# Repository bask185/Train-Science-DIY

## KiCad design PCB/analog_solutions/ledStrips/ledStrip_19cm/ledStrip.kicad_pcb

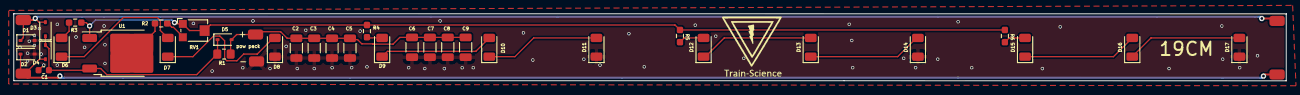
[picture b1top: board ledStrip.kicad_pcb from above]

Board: 2 copper layers, 190.0 x 10.0 mm, 35 parts (0 on the bottom side), 20 nets.

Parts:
AC2: (no value)
C1: 100nF; C_0603_1608Metric
C2, C3, C4, C5, C6, C7, C8, C9: 22uF; C_1206_3216Metric
D1, D2, D3, D4, D5: 1N4148WS; D_SOD-323
D6, D7, D8, D9, D10, D11, D12, D13, D14, D15, D16, D17: LED; LED_1206_3216Metric
R1: 100R; R_0805_handsolder-smalltext
R2: 100R; R_0603_smalltext
R3, R4, R5, R6: 10R; R_0603_smalltext
RV1: 200R; Potentiometer_Bourns_TC33X_Vertical
U1: LM317_TO-252; TO-252-2

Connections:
/Vled: R3.1, R4.1, R5.1, R6.1, RV1.1, RV1.2, U1.1 (ADJ)
AC1: D2.1 (K), D4.2 (A)
AC2: AC2.1, D1.1 (K), D3.2 (A)
GND: C1.2, C2.2, C3.2, C4.2, C5.2, C6.2, C7.2, C8.2, C9.2, D1.2 (A), D2.2 (A), D8.1 (K), D11.1 (K), D14.1 (K), D17.1 (K)
unnamed: C2.1, C3.1, C4.1, C5.1, C6.1, C7.1, C8.1, C9.1, D5.2 (A), R1.1
unnamed: D6.2 (A), R3.2
unnamed: D6.1 (K), D7.2 (A)
unnamed: D7.1 (K), D8.2 (A)
unnamed: D9.2 (A), R4.2
unnamed: D9.1 (K), D10.2 (A)
unnamed: D10.1 (K), D11.2 (A)
unnamed: D12.2 (A), R5.2
unnamed: D12.1 (K), D13.2 (A)
unnamed: D13.1 (K), D14.2 (A)
unnamed: D15.2 (A), R6.2
unnamed: D15.1 (K), D16.2 (A)
unnamed: D16.1 (K), D17.2 (A)
unnamed: R2.2, RV1.3
unnamed: R2.1, U1.2 (VO)
VCC: C1.1, D3.1 (K), D4.1 (K), D5.1 (K), R1.2, U1.3 (VI)

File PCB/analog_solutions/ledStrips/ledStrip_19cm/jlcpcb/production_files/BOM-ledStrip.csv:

Comment,Designator,Footprint,LCSC
22uF,"C2,C3,C4,C5,C6,C7,C8,C9",C_1206_3216Metric,C12891
100nF,C1,C_0603_1608Metric,C14663
100R,R1,R_0805_handsolder-smalltext,C17408
1N4148WS,"D1,D2,D3,D4,D5",D_SOD-323,C2128
LED,"D10,D11,D12,D13,D14,D15,D16,D17,D6,D7,D8,D9",LED_1206_3216Metric,C219232
100R,R2,R_0603_smalltext,C22775
10R,"R3,R4,R5,R6",R_0603_smalltext,C22859
200R,RV1,Potentiometer_Bourns_TC33X_Vertical,C720646
LM317_TO-252,U1,TO-252-2,C75510

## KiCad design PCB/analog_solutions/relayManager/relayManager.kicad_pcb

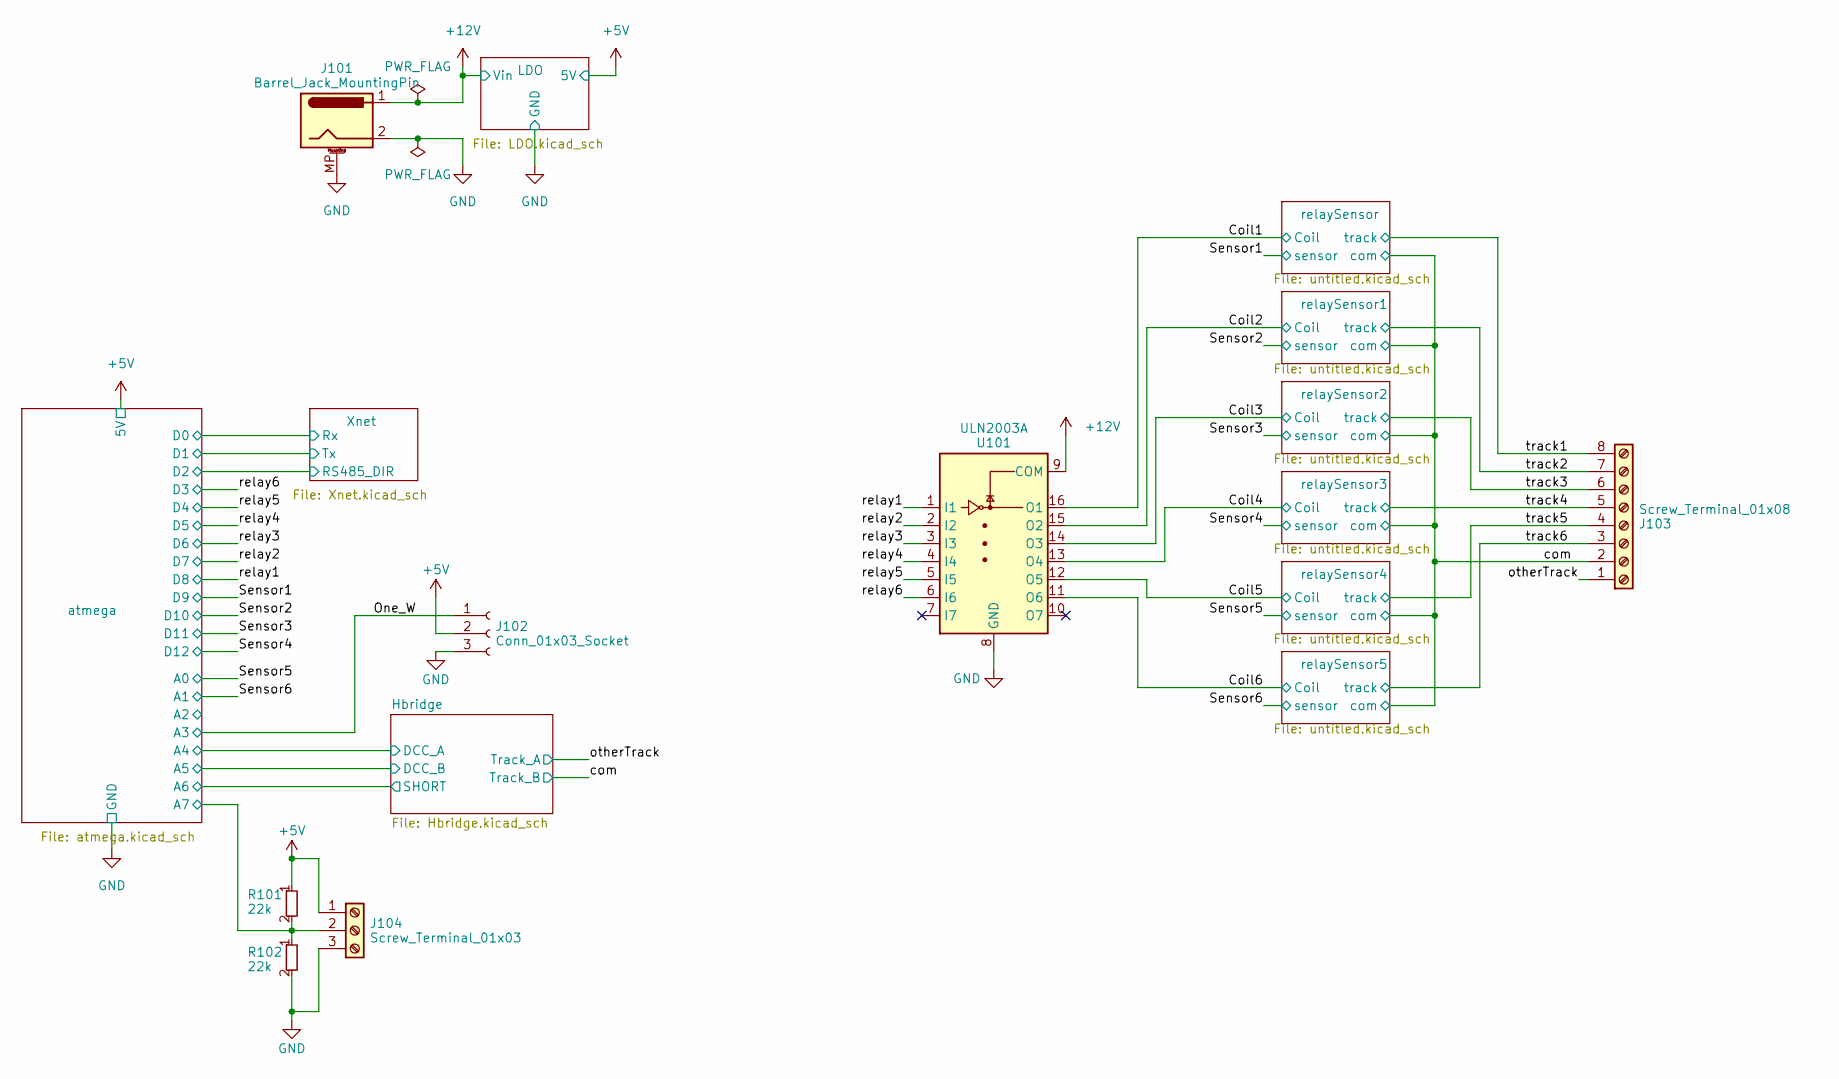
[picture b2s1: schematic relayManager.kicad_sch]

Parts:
J101: Barrel_Jack_MountingPin; barreljack
J102: Conn_01x03_Socket; PinHeader_1x03_P2.54mm_Vertical
J103: Screw_Terminal_01x08; TerminalBlock_Phoenix_MKDS-1,5-8-5.08_1x08_P5.08mm_Horizont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
J104: Screw_Terminal_01x03; TerminalBlock_Phoenix_MKDS-1,5-3-5.08_1x03_P5.08mm_Horizont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
R101, R102: 22k; R_0603_smalltext; JLCPCB Part# C31850
U101: ULN2003A; SOIC-16W_5.3x10.2mm_P1.27mm; JLCPCB Part# C7512

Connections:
+5V: J102.2, J104.1, R101.1; also elsewhere on the board
+12V: J101.1, U101.9 (COM); also elsewhere on the board
/Coil1: U101.16 (O1); also elsewhere on the board
/Coil2: U101.15 (O2); also elsewhere on the board
/Coil3: U101.14 (O3); also elsewhere on the board
/Coil4: U101.13 (O4); also elsewhere on the board
/Coil5: U101.12 (O5); also elsewhere on the board
/Coil6: U101.11 (O6); also elsewhere on the board
/One_W: J102.1; also elsewhere on the board
/atmega/A7: J104.2, R101.2, R102.1; also elsewhere on the board
/com: J103.2; also elsewhere on the board
/otherTrack: J103.1; also elsewhere on the board
/relay1: U101.1 (I1); also elsewhere on the board
/relay2: U101.2 (I2); also elsewhere on the board
/relay3: U101.3 (I3); also elsewhere on the board
/relay4: U101.4 (I4); also elsewhere on the board
/relay5: U101.5 (I5); also elsewhere on the board
/relay6: U101.6 (I6); also elsewhere on the board
/track1: J103.8; also elsewhere on the board
/track2: J103.7; also elsewhere on the board
/track3: J103.6; also elsewhere on the board
/track4: J103.5; also elsewhere on the board
/track5: J103.4; also elsewhere on the board
/track6: J103.3; also elsewhere on the board
GND: J101.2, J101.MP (MountPin), J102.3, J104.3, R102.2, U101.8 (GND); also elsewhere on the board

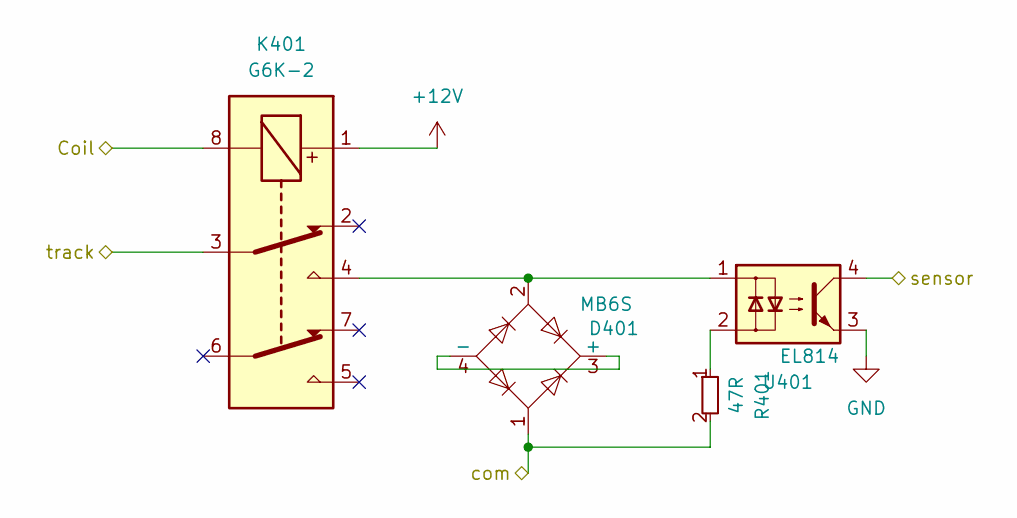
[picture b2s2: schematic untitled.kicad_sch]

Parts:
D401: MB6S; TO-269AA; JLCPCB Part# C2488
K401: G6K-2; Relay_DPDT_Omron_G6K-2F-Y; JLCPCB Part# C397192
R401: 47R; R_0603_smalltext; JLCPCB Part# C23182
U401: EL814; SMDIP-4_W9.53mm; JLCPCB Part# C500388

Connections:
+12V: K401.1; also elsewhere on the board
/Coil1: K401.8; also elsewhere on the board
/Sensor1: U401.4; also elsewhere on the board
/com: D401.1, R401.2; also elsewhere on the board
/track1: K401.3; also elsewhere on the board
GND: U401.3; also elsewhere on the board
unnamed: D401.3 (+), D401.4 (-)
unnamed: D401.2, K401.4, U401.1
unnamed: R401.1, U401.2

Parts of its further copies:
D501, D601, D701, D801, D901: MB6S; TO-269AA; JLCPCB Part# C2488
K501, K601, K701, K801, K901: G6K-2; Relay_DPDT_Omron_G6K-2F-Y; JLCPCB Part# C397192
R501, R601, R701, R801, R901: 47R; R_0603_smalltext; JLCPCB Part# C23182
U501, U601, U701, U801, U901: EL814; SMDIP-4_W9.53mm; JLCPCB Part# C500388

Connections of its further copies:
+12V: K501.1, K601.1, K701.1, K801.1, K901.1; also elsewhere on the board
/Coil2: K501.8; also elsewhere on the board
/Coil3: K601.8; also elsewhere on the board
/Coil4: K701.8; also elsewhere on the board
/Coil5: K801.8; also elsewhere on the board
/Coil6: K901.8; also elsewhere on the board
/Sensor2: U501.4; also elsewhere on the board
/Sensor3: U601.4; also elsewhere on the board
/Sensor4: U701.4; also elsewhere on the board
/Sensor5: U801.4; also elsewhere on the board
/Sensor6: U901.4; also elsewhere on the board
/com: D501.1, D601.1, D701.1, D801.1, D901.1, R501.2, R601.2, R701.2, R801.2, R901.2; also elsewhere on the board
/track2: K501.3; also elsewhere on the board
/track3: K601.3; also elsewhere on the board
/track4: K701.3; also elsewhere on the board
/track5: K801.3; also elsewhere on the board
/track6: K901.3; also elsewhere on the board
GND: U501.3, U601.3, U701.3, U801.3, U901.3; also elsewhere on the board
unnamed: D501.3 (+), D501.4 (-)
unnamed: D501.2, K501.4, U501.1
unnamed: D601.3 (+), D601.4 (-)
unnamed: D601.2, K601.4, U601.1
unnamed: D701.3 (+), D701.4 (-)
unnamed: D701.2, K701.4, U701.1
unnamed: D801.3 (+), D801.4 (-)
unnamed: D801.2, K801.4, U801.1
unnamed: D901.3 (+), D901.4 (-)
unnamed: D901.2, K901.4, U901.1
unnamed: R501.1, U501.2
unnamed: R601.1, U601.2
unnamed: R701.1, U701.2
unnamed: R801.1, U801.2
unnamed: R901.1, U901.2

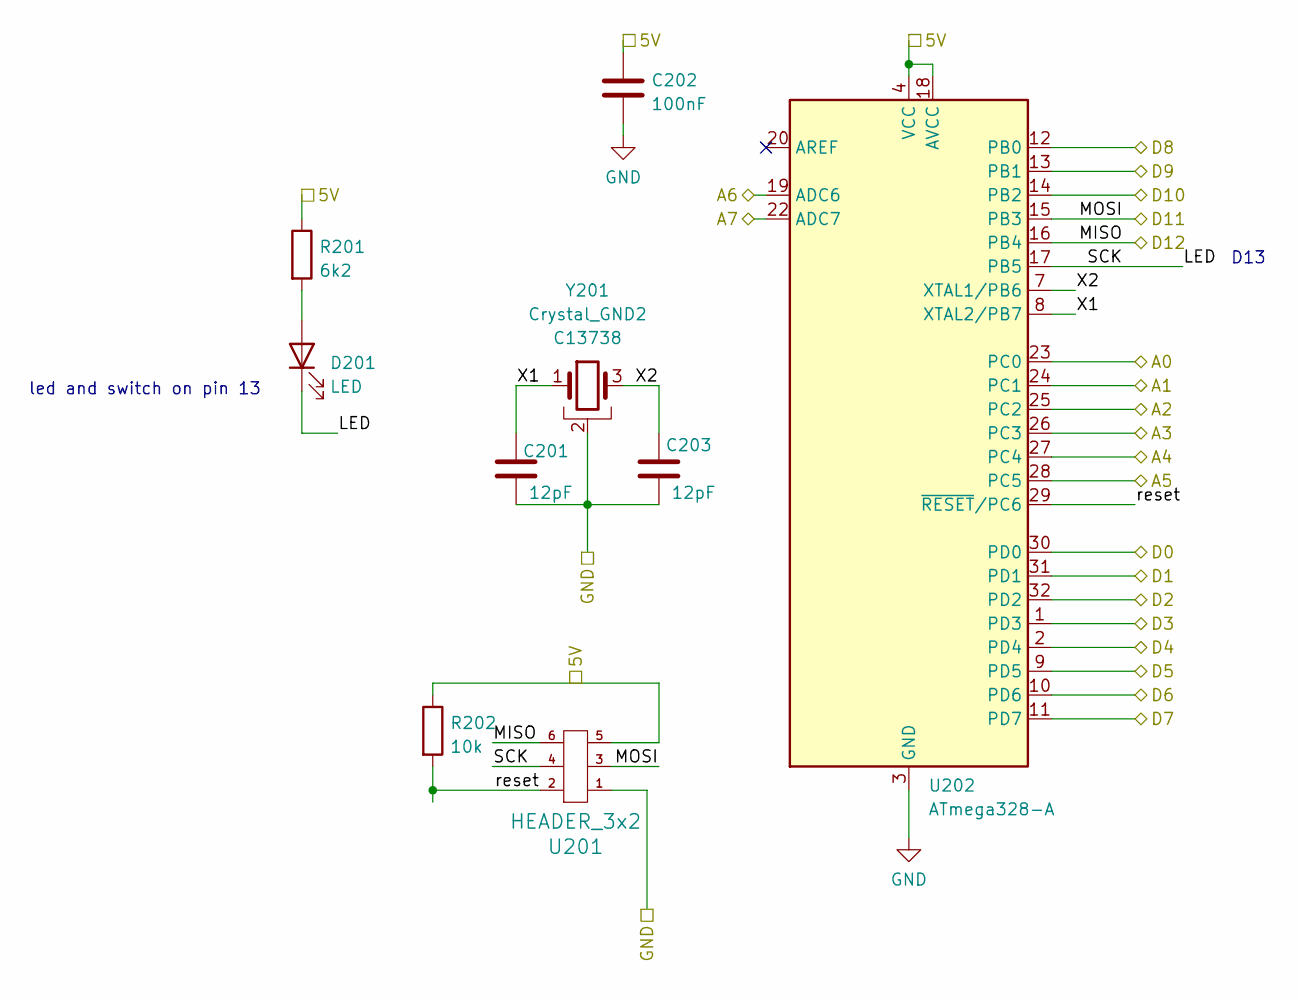
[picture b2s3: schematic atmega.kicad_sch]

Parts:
C201: 12pF; C_0805_2012Metric_Pad1.18x1.45mm_HandSolder
C202: 100nF; C_0603_1608Metric_Pad1.08x0.95mm_HandSolder; JLCPCB Part# C14663
C203: 12pF; C_0805_2012Metric_Pad1.18x1.45mm_HandSolder; JLCPCB Part# C1792
D201: LED; LED_0805_2012Metric_Pad1.15x1.40mm_HandSolder; JLCPCB Part# C84256
R201: 6k2; R_0603_1608Metric_Pad0.98x0.95mm_HandSolder; JLCPCB Part# C4260
R202: 10k; R_0402_1005Metric_Pad0.72x0.64mm_HandSolder; JLCPCB Part# C25744
U201: HEADER_3x2; PinSocket_2x03_P1.27mm_Vertical
U202: ATmega328-A; TQFP-32_7x7mm_P0.8mm; JLCPCB Part# C14877
Y201: Crystal_GND2; crystal_arduino; JLCPCB Part# C13738

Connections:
+5V: C202.2, R201.1, R202.1, U201.5, U202.4 (VCC), U202.6 (VCC), U202.18 (AVCC); also elsewhere on the board
/Hbridge/DCC_A: U202.27 (PC4); also elsewhere on the board
/Hbridge/DCC_B: U202.28 (PC5); also elsewhere on the board
/Hbridge/SHORT: U202.19 (ADC6); also elsewhere on the board
/One_W: U202.26 (PC3); also elsewhere on the board
/Sensor1: U202.13 (PB1); also elsewhere on the board
/Sensor2: U202.14 (PB2); also elsewhere on the board
/Sensor3: U201.3, U202.15 (PB3); also elsewhere on the board
/Sensor4: U201.6, U202.16 (PB4); also elsewhere on the board
/Sensor5: U202.23 (PC0); also elsewhere on the board
/Sensor6: U202.24 (PC1); also elsewhere on the board
/Xnet/RS485_DIR: U202.32 (PD2); also elsewhere on the board
/Xnet/Rx: U202.30 (PD0); also elsewhere on the board
/Xnet/Tx: U202.31 (PD1); also elsewhere on the board
/atmega/A2: U202.25 (PC2)
/atmega/A7: U202.22 (ADC7); also elsewhere on the board
/atmega/LED: D201.1 (K), U201.4, U202.17 (PB5)
/atmega/X1: C201.2, U202.8 (XTAL2/PB7), Y201.1
/atmega/X2: C203.2, U202.7 (XTAL1/PB6), Y201.3
/atmega/reset: R202.2, U201.2, U202.29 (~RESET/PC6)
/relay1: U202.12 (PB0); also elsewhere on the board
/relay2: U202.11 (PD7); also elsewhere on the board
/relay3: U202.10 (PD6); also elsewhere on the board
/relay4: U202.9 (PD5); also elsewhere on the board
/relay5: U202.2 (PD4); also elsewhere on the board
/relay6: U202.1 (PD3); also elsewhere on the board
GND: C201.1, C202.1, C203.1, U201.1, U202.3 (GND), U202.5 (GND), U202.21 (GND), Y201.2 (GND), Y201.4 (GND); also elsewhere on the board
unnamed: D201.2 (A), R201.2

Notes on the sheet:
led and switch on pin 13
D13

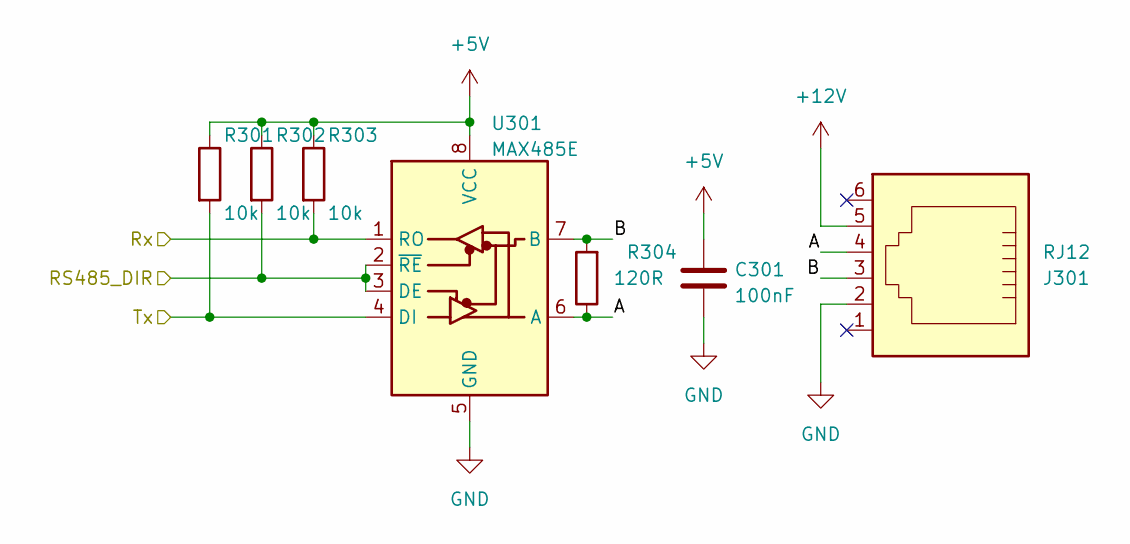
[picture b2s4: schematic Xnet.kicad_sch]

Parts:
C301: 100nF; C_0603_1608Metric; JLCPCB Part# C14663
J301: RJ12
R301, R302, R303: 10k; R_0402_1005Metric; JLCPCB Part# C25744
R304: 120R; R_0805_2012Metric
U301: MAX485E; SOIC-8_3.9x4.9mm_P1.27mm; JLCPCB Part# C668206

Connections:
+5V: C301.1, R301.1, R302.1, R303.1, U301.8 (VCC); also elsewhere on the board
+12V: J301.5; also elsewhere on the board
/Xnet/A: J301.4, R304.1, U301.6 (A)
/Xnet/B: J301.3, R304.2, U301.7 (B)
/Xnet/RS485_DIR: R302.2, U301.2 (~RE), U301.3 (DE); also elsewhere on the board
/Xnet/Rx: R303.2, U301.1 (RO); also elsewhere on the board
/Xnet/Tx: R301.2, U301.4 (DI); also elsewhere on the board
GND: C301.2, J301.2, U301.5 (GND); also elsewhere on the board

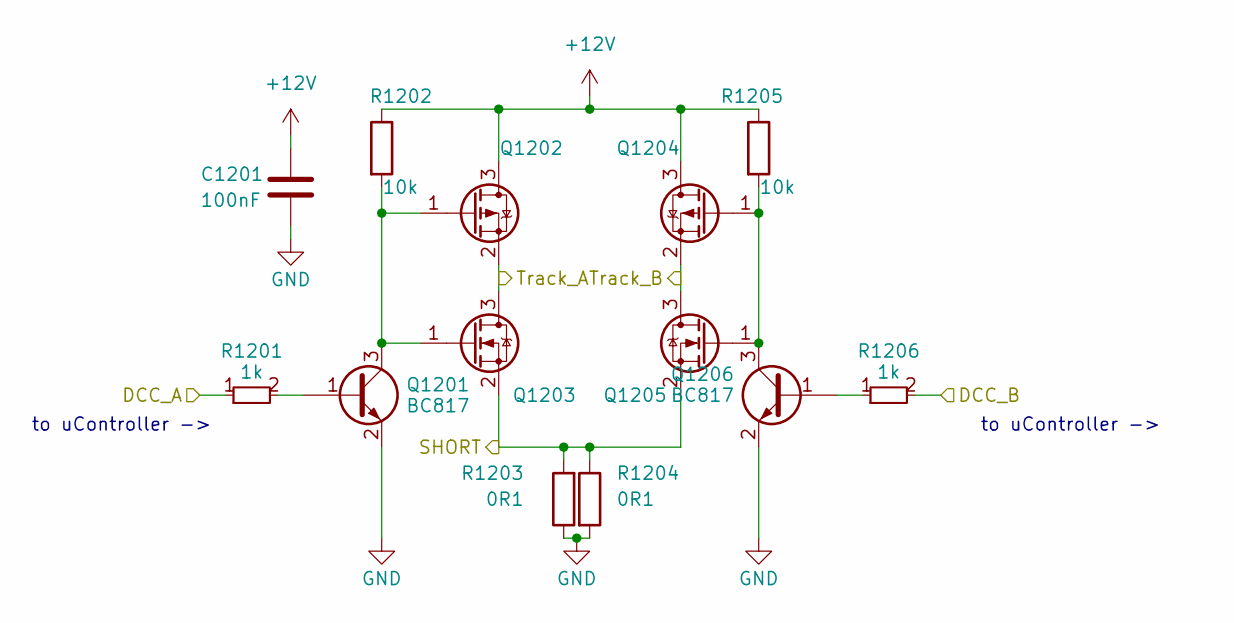
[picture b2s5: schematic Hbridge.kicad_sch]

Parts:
C1201: 100nF; C_0603_1608Metric_Pad1.08x0.95mm_HandSolder; JLCPCB Part# C14663
Q1201, Q1206: BC817; SOT-23; JLCPCB Part# C181140
Q1202, Q1204: P-channel; SOT-23
Q1203: N-Channel; SOT-23
Q1205: N-channel; SOT-23
R1201, R1206: 1k; R_0603_smalltext; JLCPCB Part# C21190
R1202, R1205: 10k; R_0603_1608Metric
R1203, R1204: 0R1; R_0805_2012Metric_Pad1.20x1.40mm_HandSolder; JLCPCB Part# C25334

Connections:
+12V: C1201.2, Q1202.3 (D), Q1204.3 (D), R1202.1, R1205.1; also elsewhere on the board
/Hbridge/DCC_A: R1201.1; also elsewhere on the board
/Hbridge/DCC_B: R1206.2; also elsewhere on the board
/Hbridge/SHORT: Q1203.2 (S), Q1205.2 (S), R1203.2, R1204.1; also elsewhere on the board
/com: Q1204.2 (S), Q1205.3 (D); also elsewhere on the board
/otherTrack: Q1202.2 (S), Q1203.3 (D); also elsewhere on the board
GND: C1201.1, Q1201.2 (E), Q1206.2 (E), R1203.1, R1204.2; also elsewhere on the board
unnamed: Q1201.1 (B), R1201.2
unnamed: Q1201.3 (C), Q1202.1 (G), Q1203.1 (G), R1202.2
unnamed: Q1204.1 (G), Q1205.1 (G), Q1206.3 (C), R1205.2
unnamed: Q1206.1 (B), R1206.1

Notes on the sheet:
to uController ->

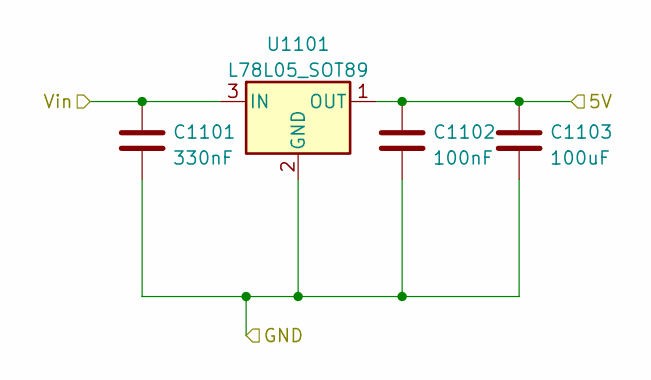
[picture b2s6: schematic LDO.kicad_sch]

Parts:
C1101: 330nF; C_0603_1608Metric_Pad1.08x0.95mm_HandSolder; JLCPCB Part# C1615
C1102: 100nF; C_0603_1608Metric_Pad1.08x0.95mm_HandSolder; JLCPCB Part# C14663
C1103: 100uF; C_1206_3216Metric_Pad1.33x1.80mm_HandSolder; JLCPCB Part# C15008
U1101: L78L05_SOT89; SOT-89-3; JLCPCB Part# C71136

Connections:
+5V: C1102.1, C1103.1, U1101.1 (OUT); also elsewhere on the board
+12V: C1101.1, U1101.3 (IN); also elsewhere on the board
GND: C1101.2, C1102.2, C1103.2, U1101.2 (GND); also elsewhere on the board

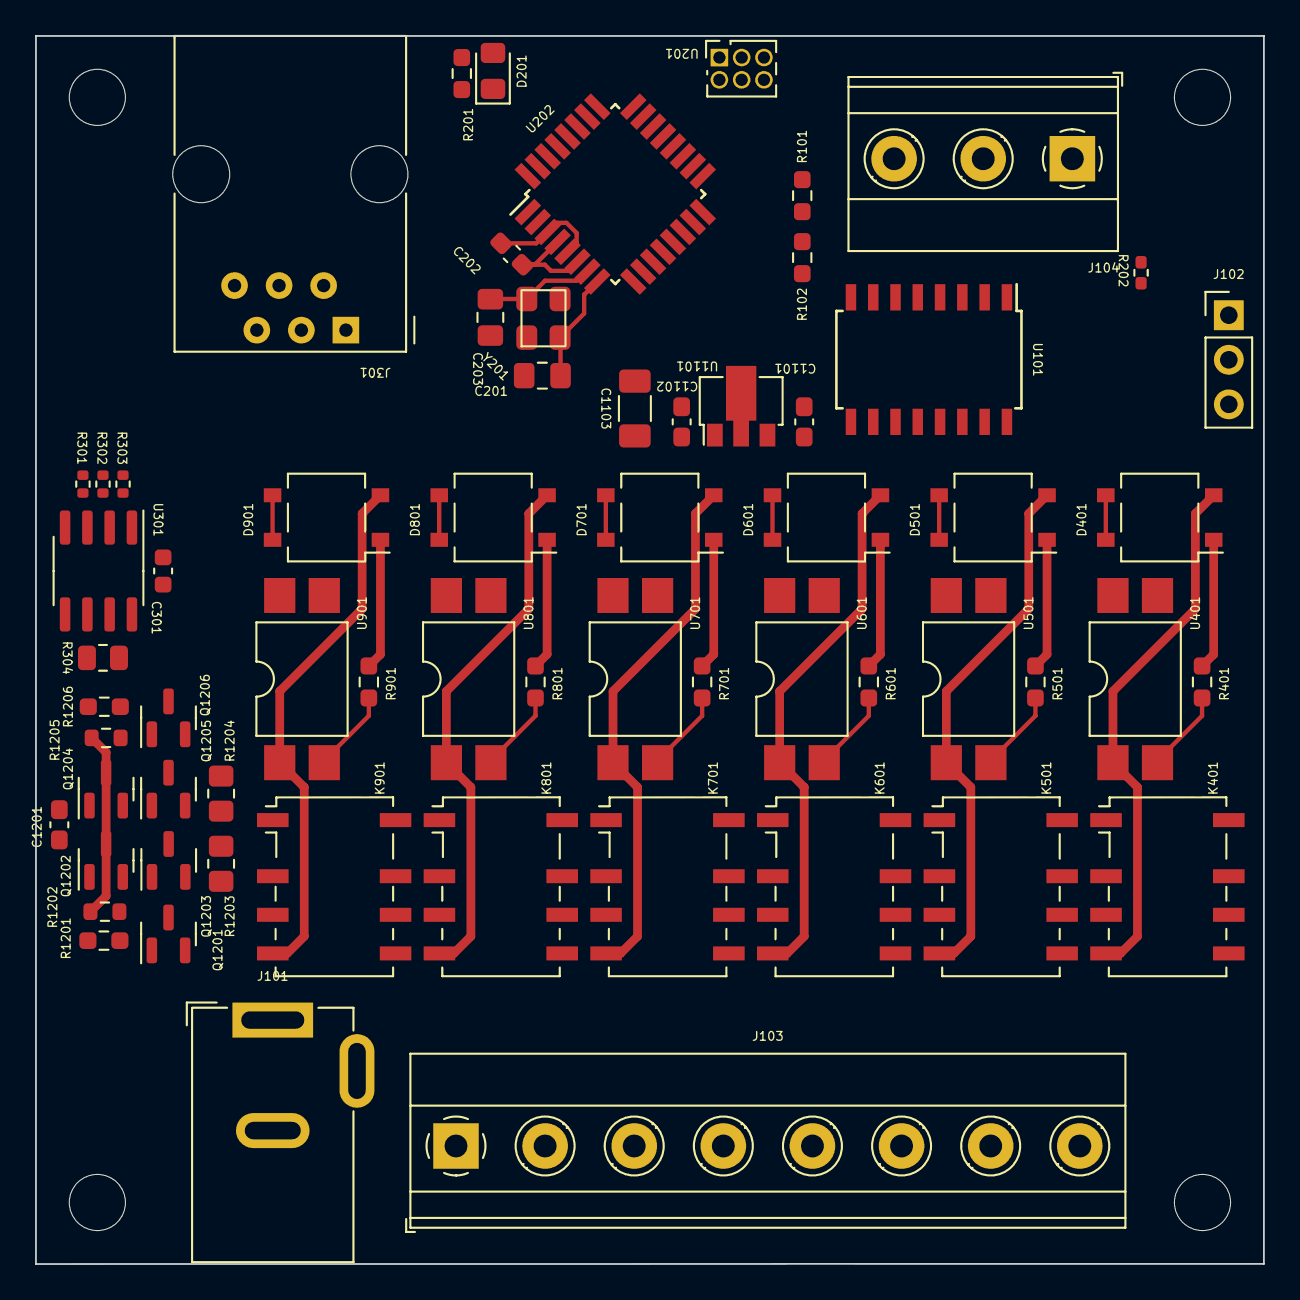
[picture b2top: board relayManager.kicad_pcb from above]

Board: 2 copper layers, 70.0 x 70.0 mm, 64 parts (0 on the bottom side), 66 nets.

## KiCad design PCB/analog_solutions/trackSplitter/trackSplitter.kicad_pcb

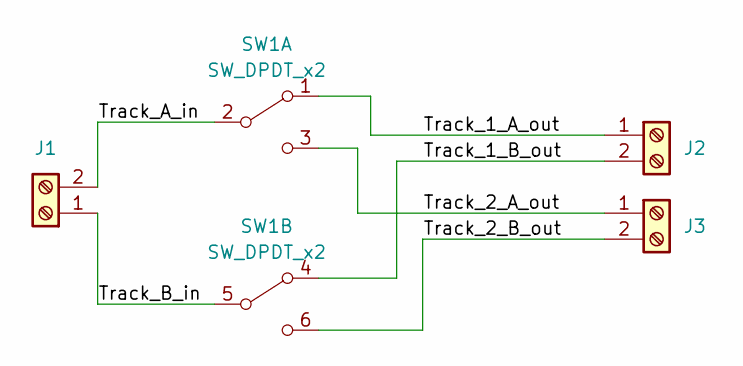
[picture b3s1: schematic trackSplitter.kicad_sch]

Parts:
J1, J2, J3: Screw_Terminal_01x02; TerminalBlock_Phoenix_MKDS-1,5-2-5.08_1x02_P5.08mm_Horizont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
SW1: SW_DPDT_x2; MTS_DPDT

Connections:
/Track_1_A_out: J2.1, SW1.1 (A)
/Track_1_B_out: J2.2, SW1.4 (A)
/Track_2_A_out: J3.1, SW1.3 (C)
/Track_2_B_out: J3.2, SW1.6 (C)
/Track_A_in: J1.2, SW1.2 (B)
/Track_B_in: J1.1, SW1.5 (B)

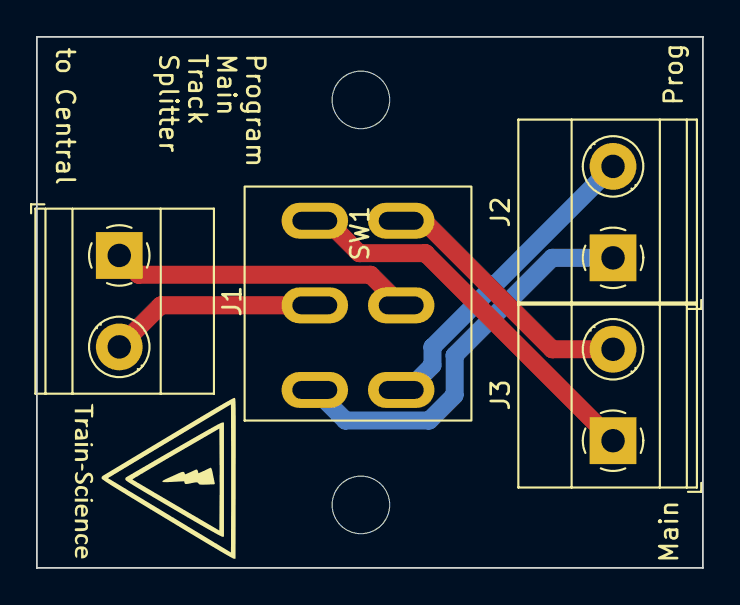
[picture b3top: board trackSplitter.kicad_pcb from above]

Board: 2 copper layers, 37.0 x 29.5 mm, 4 parts (0 on the bottom side), 6 nets.

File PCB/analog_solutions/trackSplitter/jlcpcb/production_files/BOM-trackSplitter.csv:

Comment,Designator,Footprint,LCSC
Screw_Terminal_01x02,J3,"TerminalBlock_Phoenix_MKDS-1,5-2-5.08_1x02_P5.08mm_Horizontal",
Screw_Terminal_01x02,J2,"TerminalBlock_Phoenix_MKDS-1,5-2-5.08_1x02_P5.08mm_Horizontal",
SW_DPDT_x2,SW1,MTS_DPDT,
Screw_Terminal_01x02,J1,"TerminalBlock_Phoenix_MKDS-1,5-2-5.08_1x02_P5.08mm_Horizontal",

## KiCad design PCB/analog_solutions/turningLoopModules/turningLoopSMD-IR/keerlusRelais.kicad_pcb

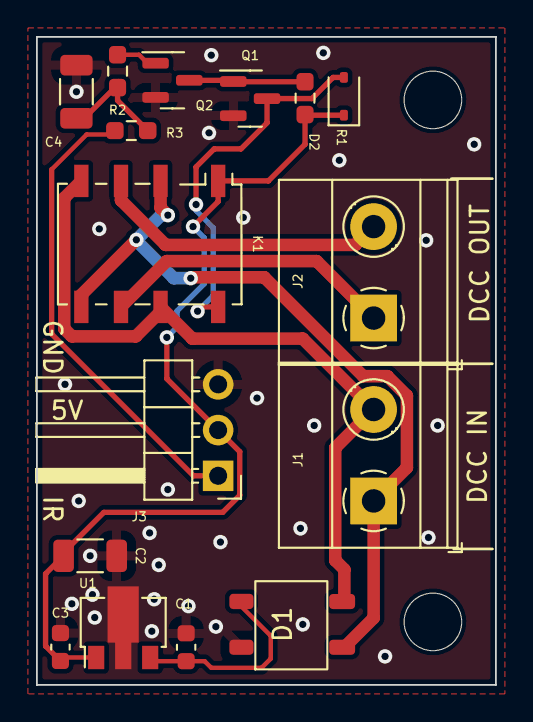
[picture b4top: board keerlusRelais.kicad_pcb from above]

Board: 2 copper layers, 25.5 x 36.0 mm, 16 parts (0 on the bottom side), 12 nets.

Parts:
C1, C3: 100nF; C_0603_1608Metric
C2, C4: 22uF; C_1206_3216Metric
D1: MB10S; MB10s
D2: 1N4148WS; D_SOD-323
J1: DCC_IN; TerminalBlock_Phoenix_MKDS-1,5-2-5.08_1x02_P5.08mm_Horizont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
J2: DCC_out; TerminalBlock_Phoenix_MKDS-1,5-2-5.08_1x02_P5.08mm_Horizont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
J3: Conn_01x03_Male; PinHeader_1x03_P2.54mm_Horizontal
K1: G6K-2F-Y-TR DC5; Relay_DPDT_Omron_G6K-2F-Y
Q1, Q2: NPN_TOR; SOT-23
R1: 10k; R_0603_smalltext
R2, R3: 4k7; R_0603_smalltext
U1: L78L12_SOT89; SOT-89-3

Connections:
+12V: C2.1, C3.2, D2.1 (K), J3.2, K1.1, R1.1, U1.1 (OUT)
/DCC_A_IN: D1.3, J1.1, K1.2, K1.5
/DCC_A_OUT: J2.1, K1.6
/DCC_B_IN: D1.4, J1.2, K1.4, K1.7
/DCC_B_OUT: J2.2, K1.3
GND: C1.1, C2.2, C3.1, C4.2, D1.2 (-), J3.3, Q1.2 (E), Q2.2 (E), U1.2 (GND)
unnamed: C4.1, R2.2, R3.1
unnamed: D2.2 (A), K1.8, Q1.3 (C)
unnamed: J3.1, R3.2
unnamed: Q1.1 (B), Q2.3 (C), R1.2
unnamed: Q2.1 (B), R2.1
VCC: C1.2, D1.1 (+), U1.3 (IN)

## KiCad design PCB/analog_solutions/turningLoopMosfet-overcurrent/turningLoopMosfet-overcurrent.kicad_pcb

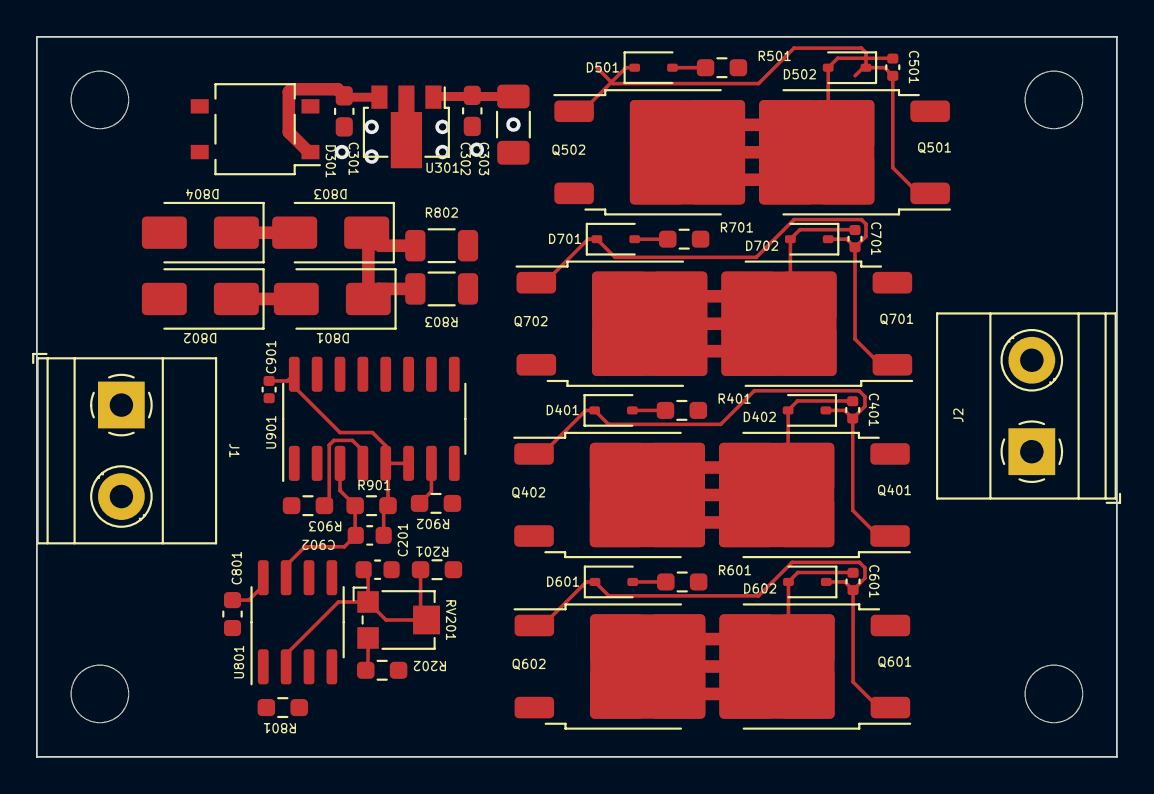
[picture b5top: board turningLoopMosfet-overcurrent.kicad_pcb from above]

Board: 2 copper layers, 60.0 x 40.0 mm, 50 parts (0 on the bottom side), 28 nets.

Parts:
C201, C801: 100nF; C_0603_1608Metric
C301: 330nF; C_0603_1608Metric_Pad1.08x0.95mm_HandSolder
C302: 100nF; C_0603_1608Metric_Pad1.08x0.95mm_HandSolder
C303: 100uF; C_1206_3216Metric_Pad1.33x1.80mm_HandSolder
C401, C501, C601, C701, C901: 100nF; C_0402_1005Metric
C902: 10pF; C_0603_1608Metric
D301: MB10S; TO-269AA
D401, D402, D501, D502, D601, D602, D701, D702: 1N4148WS; D_SOD-323
D801, D802, D803, D804: SS53; D_SMA
J1, J2: Screw_Terminal_01x02; TerminalBlock_Phoenix_MKDS-1,5-2-5.08_1x02_P5.08mm_Horizont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
Q401, Q402, Q501, Q502, Q601, Q602, Q701, Q702: MDD50N03D; TO-252-2
R201, R901: 10k; R_0603_smalltext
R202: 150R; R_0603_smalltext
R401, R501, R601, R701: 100R; R_0603_smalltext
R801: 4k7; R_0603_smalltext
R802, R803: 0R1; R_1206_3216Metric
R902, R903: 22k; R_0603_smalltext
RV201: 200R; Potentiometer_Bourns_TC33X_Vertical
U301: L78L05_SOT89; SOT-89-3
U801: LM311; SOIC-8_3.9x4.9mm_P1.27mm
U901: 4027; SOIC-16_3.9x9.9mm_P1.27mm

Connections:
+5V: C302.1, C303.1, C801.2, R201.1, U301.1 (OUT), U801.8 (V+)
/DCC_IN_A: D301.4, D801.2 (A), D802.1 (K), J1.1
/DCC_IN_B: D301.3, J1.2, Q602.3 (S), Q702.3 (S)
/DCC_OUT_A: J2.1, Q401.3 (S), Q601.3 (S)
/DCC_OUT_B: J2.2, Q501.3 (S), Q701.3 (S)
/Mosfets1/GATE: R401.1, R701.1, U901.2 (~Q)
/Mosfets1/IN: D803.2 (A), D804.1 (K), Q402.3 (S), Q502.3 (S)
/Mosfets2/GATE: R501.1, R601.1, U901.1 (Q)
/Vref/Vref: C201.2, R201.2, RV201.1, RV201.2, U801.2 (+)
/compA/clock: C902.2, R901.1, U801.7, U901.3 (C)
GND: C201.1, C301.2, C302.2, C303.2, C801.1, C901.2, D301.2 (-), D802.2 (A), D804.2 (A), R202.2, R801.2, R802.2, R803.1, R902.1, R903.2, U301.2 (GND), U801.1 (GND), U801.4 (V-), U901.8 (VSS)
unnamed: D401.2 (A), R401.2
unnamed: C401.2, D401.1 (K), D402.1 (K), Q401.1 (G), Q402.1 (G)
unnamed: C401.1, D402.2 (A), Q401.2 (D), Q402.2 (D)
unnamed: D501.2 (A), R501.2
unnamed: C501.2, D501.1 (K), D502.1 (K), Q501.1 (G), Q502.1 (G)
unnamed: C501.1, D502.2 (A), Q501.2 (D), Q502.2 (D)
unnamed: D601.2 (A), R601.2
unnamed: C601.2, D601.1 (K), D602.1 (K), Q601.1 (G), Q602.1 (G)
unnamed: C601.1, D602.2 (A), Q601.2 (D), Q602.2 (D)
unnamed: D701.2 (A), R701.2
unnamed: C701.2, D701.1 (K), D702.1 (K), Q701.1 (G), Q702.1 (G)
unnamed: C701.1, D702.2 (A), Q701.2 (D), Q702.2 (D)
unnamed: D801.1 (K), D803.1 (K), R801.1, R802.1, R803.2, U801.3 (-)
unnamed: R202.1, RV201.3
unnamed: R903.1, U901.4 (R)
unnamed: R902.2, U901.7 (S)
VCC: C301.1, C901.1, C902.1, D301.1 (+), R901.2, U301.3 (IN), U901.5 (K), U901.6 (J), U901.16 (VDD)
